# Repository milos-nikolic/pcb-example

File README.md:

# This is basic pcb design example

## With dual-layer

## With single-layer

## Produced ( ordered boards )

## Populated

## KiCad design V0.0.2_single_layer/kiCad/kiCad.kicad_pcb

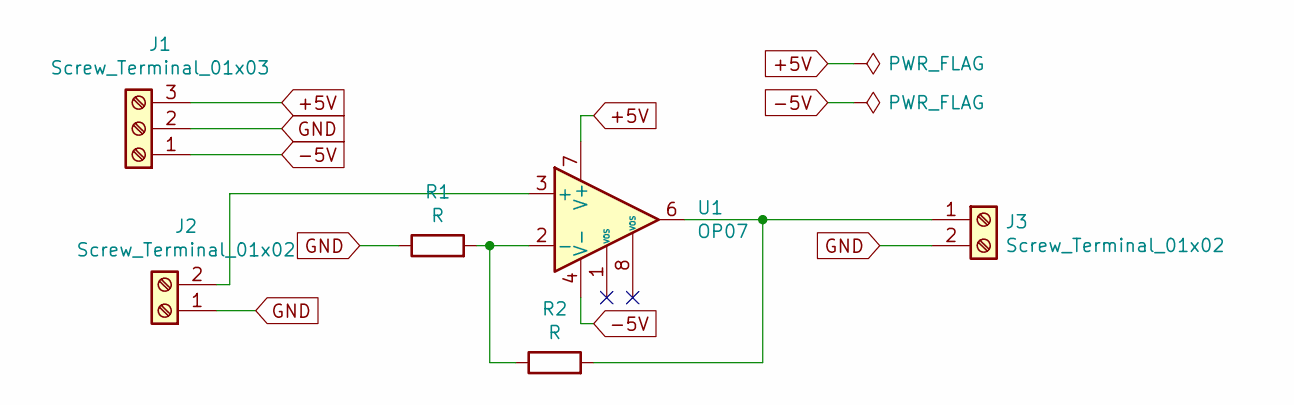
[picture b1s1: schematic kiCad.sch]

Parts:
J1: Screw_Terminal_01x03; TerminalBlock_bornier-3_P5.08mm
J2, J3: Screw_Terminal_01x02; TerminalBlock_bornier-2_P5.08mm
R1, R2: R; R_Axial_DIN0207_L6.3mm_D2.5mm_P10.16mm_Horizontal
U1: OP07; DIP-8_W10.16mm_LongPads

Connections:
+5V: J1.3, U1.7 (V+)
-5V: J1.1, U1.4 (V-)
GND: J1.2, J2.1, J3.2, R1.1
unnamed: J2.2, U1.3 (+)
unnamed: J3.1, R2.2, U1.6
unnamed: R1.2, R2.1, U1.2 (-)

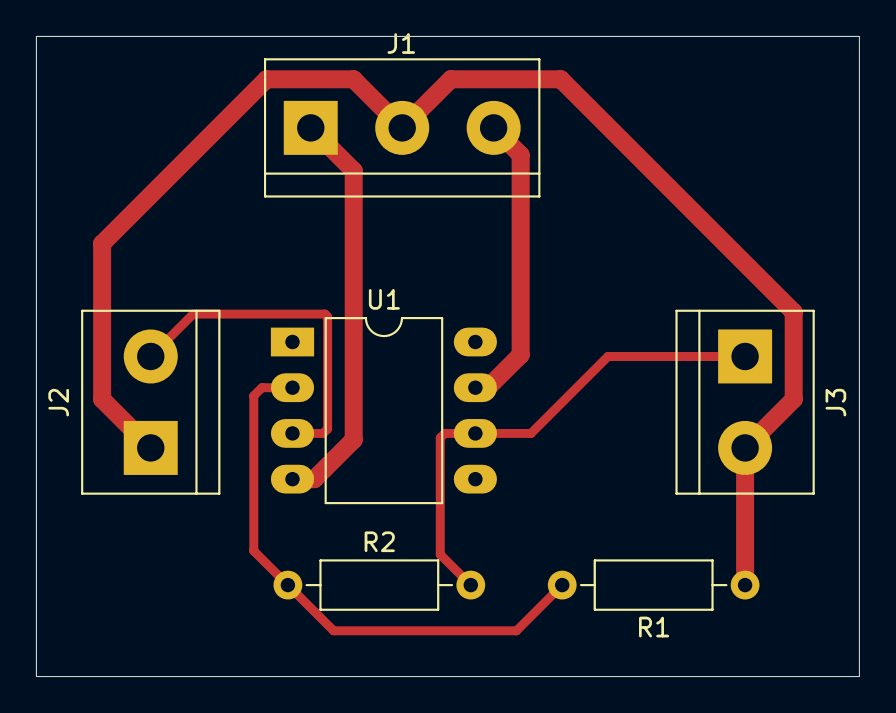
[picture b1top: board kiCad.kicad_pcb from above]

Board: 2 copper layers, 45.7 x 35.6 mm, 6 parts (0 on the bottom side), 6 nets.

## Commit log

2020-07-27 Added examples.
2020-07-27 Updated md description.
2020-07-27 Minor spelling corection.
2020-08-05 Added pictures of produced boards.
2020-08-05 Updated readme.
